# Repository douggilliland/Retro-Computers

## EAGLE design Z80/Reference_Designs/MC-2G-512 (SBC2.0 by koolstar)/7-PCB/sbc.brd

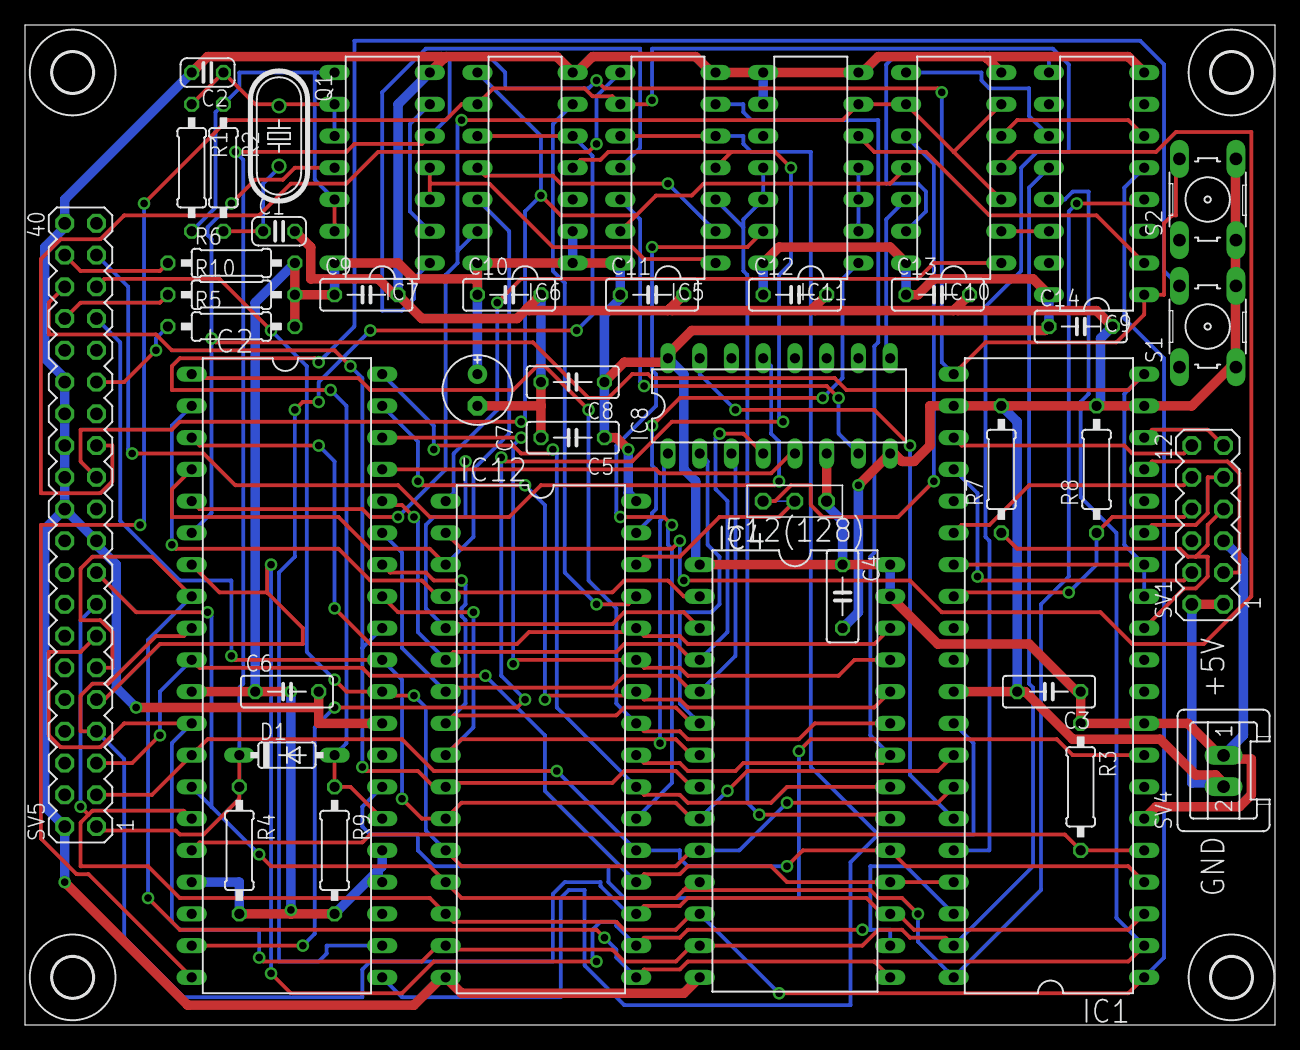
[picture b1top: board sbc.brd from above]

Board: 2 copper layers, 100.0 x 80.0 mm, 47 parts (0 on the bottom side), 74 nets.

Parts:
C1, C2: 22p; C025-024X044
C3, C4, C5, C6, C8, C9, C10, C11, C12, C13, C14: 100n; C050-025X075
C7: .47m; E2,5-6E
D1: 1N4148; DO35-7
H1, H2, H3, H4: 3.2; 3,2
IC1: Z84C4010 SIO/0; DIL40
IC2: Z84C0006; DIL40
IC4: 27C128; DIL28-6
IC5, IC6: 74HCT32; DIL14
IC7: 74HCT00; DIL14
IC8: 74HCT138; DIL16
IC9: 74HCT175; DIL16
IC10, IC11: 74HCT02; DIL14
IC12: AS6C4008 (1008); DIL32
Q1: 7.3728 MHz; HC49U-V
R1: 1M; 0207/10
R2: 1k; 0207/10
R3, R4, R5, R6, R9, R10: 4k7; 0207/10
R7, R8: 10k; 0207/10
S1: WARM; B3F-10XX
S2: COLD; B3F-10XX
SV1: TTY A/B; MA06-2
SV4: IDE Power; S02P
SV5: IDE-CF; MA20-2
U$1: JMP2; JUMP2

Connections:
A0: IC1.34, IC2.30, IC4.10, IC12.12, SV5.35
A1: IC1.33, IC2.31, IC4.9, IC12.11, SV5.33
A2: IC2.32, IC4.8, IC12.10, SV5.36
A3: IC2.33, IC4.7, IC8.1, IC12.9
A4: IC2.34, IC4.6, IC8.2, IC12.8
A5: IC2.35, IC4.5, IC8.3, IC12.7
A6: IC2.36, IC4.4, IC8.4, IC12.6
A7: IC2.37, IC4.3, IC8.5, IC12.5
A8: IC2.38, IC4.25, IC12.27
A9: IC2.39, IC4.24, IC12.26
A10: IC2.40, IC4.21, IC12.23
A11: IC2.1, IC4.23, IC12.25
A12: IC2.2, IC4.2, IC12.4
A13: IC2.3, IC4.26, IC12.28
A14: IC2.4, IC6.12, IC12.3
A15: IC2.5, IC6.13, IC10.3, IC10.6, IC10.9, IC11.6
CLK: IC1.13, IC1.14, IC1.20, IC1.27, IC2.6, IC7.11
CTA: IC1.18, SV1.11
CTB: IC1.23, SV1.12
D0: IC1.40, IC2.14, IC4.11, IC9.4, IC12.13, SV5.17
D1: IC1.1, IC2.15, IC4.12, IC9.5, IC12.14, SV5.15
D2: IC1.39, IC2.12, IC4.13, IC9.12, IC12.15, SV5.13
D3: IC1.2, IC2.8, IC4.15, IC9.13, IC12.17, SV5.11
D4: IC1.38, IC2.7, IC4.16, IC12.18, SV5.9
D5: IC1.3, IC2.9, IC4.17, IC12.19, SV5.7
D6: IC1.37, IC2.10, IC4.18, IC12.20, SV5.5
D7: IC1.4, IC2.13, IC4.19, IC12.21, SV5.3
GND: C1.2, C2.2, C3.2, C4.2, C5.2, C6.2, C7.-, C8.2, C9.2, C10.2, C11.2, C12.2, C13.2, C14.2, IC1.19, IC1.22, IC1.31, IC2.29, IC4.14, IC5.7, IC6.7, IC7.7, IC8.8, IC9.8, IC10.7, IC11.7, IC11.8, IC11.9, IC12.16, R7.2, R8.2, S1.3, S1.4, S2.3, S2.4, SV1.1, SV1.2, SV4.2, SV5.2, SV5.19, SV5.22, SV5.24, SV5.26, SV5.28, SV5.30, SV5.40
INT: IC1.5, IC2.16, R3.2
IORD: IC5.8, SV5.25
IOREQ: IC1.36, IC2.20, IC5.9, IC6.9
IOWR: IC5.13, IC6.8, IC10.11, SV5.23
M1: IC1.8, IC2.27
M15: IC11.1, IC12.31
M16: IC10.4, IC12.2
M17: IC10.10, U$1.1
M18: IC10.1, IC12.1
MEMRD: IC4.22, IC5.6, IC12.24
MEMWR: IC6.6, IC12.29
MREQ: IC2.19, IC5.4, IC6.4
unnamed: IC9.6, IC10.5
unnamed: IC9.2, IC11.5
unnamed: IC7.2, IC7.6
unnamed: IC5.11, IC7.1
unnamed: C2.1, IC7.9, IC7.10, Q1.1, R1.1
unnamed: C1.1, Q1.2, R2.2
unnamed: IC5.2, IC6.11
unnamed: IC5.1, IC7.3, IC7.4
unnamed: IC7.8, IC7.12, IC7.13, R1.2, R2.1
unnamed: IC9.11, IC10.8
unnamed: IC9.14, IC10.2
unnamed: IC11.2, IC11.3, IC11.4
unnamed: IC12.30, U$1.2
unnamed: IC9.9, IC10.13
unnamed: R6.1, SV5.38
unnamed: R10.1, SV5.34
unnamed: R5.1, SV5.29
RAMS: IC11.13, IC12.22
RD: IC1.32, IC2.21, IC5.5, IC5.10
RESET: D1.C, IC1.21, IC7.5, IC9.1, R4.1, S2.2, SV5.1
ROMS: IC4.20, IC5.3, IC11.11, IC11.12
RTA: IC1.17, SV1.3
RTB: IC1.24, SV1.4
RXA: IC1.12, R7.1, SV1.7
RXB: IC1.28, R8.1, SV1.8
TXA: IC1.15, SV1.9
TXB: IC1.26, SV1.10
VCC: C3.1, C4.1, C5.1, C6.1, C7.+, C8.1, C9.1, C10.1, C11.1, C12.1, C13.1, C14.1, IC1.6, IC1.9, IC2.11, IC2.17, IC2.24, IC2.25, IC4.1, IC4.27, IC4.28, IC5.14, IC6.1, IC6.2, IC6.14, IC7.14, IC8.6, IC8.16, IC9.16, IC10.14, IC11.14, IC12.32, R3.1, R4.2, R5.2, R6.2, R9.2, R10.2, SV1.5, SV4.1, U$1.3
WR: IC2.22, IC6.5, IC6.10
WRESET: D1.A, IC2.26, R9.1, S1.2
Y0: IC1.35, IC8.15
Y2: IC8.13, SV5.37
Y6: IC8.9, IC10.12
Y7: IC5.12, IC8.7

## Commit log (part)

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2022-04-15 retro stuff
2022-04-17 Some more FPGA builds
2022-04-18 Builds
2022-04-19 PDP-11 Builds
2022-04-21 docs added
2022-04-23 WORKING TINYBASIC
2022-04-26 FigFORTH works
2022-04-27 FIX LABELS
2022-04-27 Forth in ROM build WIP
2022-04-28 More FIG-Forth docs/builds
2022-04-28 Move files
2022-04-29 Extended RAM test
2022-04-29 External SRAM test works
2022-04-29 More comments
2022-04-29 Fix comments
2022-04-29 PDP-8 and PDP-11 builds
2022-04-30 Make In Box versions of PDP-11
2022-04-30 Built In Box version of PDP-11/45 and PDP-11/70
2022-05-01 More builds
2022-05-01 Another PDP-11 variant plus Forth stuff
2022-05-01 PDP-11/45 in MultiComp box - boots
2022-05-01 Working - Boots RT11V5
2022-05-01 Shuffle PDP-11 docs folders
2022-05-01 Fixed serial port define so SW4 works
2022-05-01 PDP-11/70 in box works
2022-05-02 FLEX DOCS
2022-05-03 6502 stuff
2022-05-09 Working on SD card OS
2022-05-10 Shuffle around OSI OS
2022-05-10 Move helo.c
2022-05-10 Shuffle around folders
2022-05-11 STREAMLINE SD CARD CODE
2022-05-11 ADD CLUSTER OFFSET
2022-05-11 Dump sector number in DIR listing
    Allow user to enter sector number and dump buffer
    Working well
2022-05-13 UK101 C1P docs
2022-05-13 Shuffle OSI files
2022-05-13 More shuffling file
2022-05-30 Shuffle stuff
2022-08-18 DABUG
2022-08-18 Journals
2022-08-18 More OSI
2022-08-19 More OSI stuff
2022-08-26 docs
2022-08-26 TG68 box
2022-09-06 Z80_PSoC code
2022-09-06 Schematic cleanups
2022-09-07 IMPROVEMENTS TO START-UP
2022-09-18 Minor menu tweeks
2022-09-20 65C816 DOCS
2022-09-24 CORSHAM 6800 xSWTBUG
2022-09-25 CORSHAM STUFF
2022-10-06 Bump addressable from 2.7.0 to 2.8.1 in /6502/planck-6502/docs
    Bumps [addressable](https://github.com/sporkmonger/addressable) from 2.7.0 to 2.8.1.
    - [Release notes](https://github.com/sporkmonger/addressable/releases)
    - [Changelog](https://github.com/sporkmonger/addressable/blob/main/CHANGELOG.md)
    - [Commits](https://github.com/sporkmonger/addressable/compare/addressable-2.7.0...addressable-2.8.1)
    ---
    updated-dependencies:
2023-03-15 68K retro
2023-03-30 TinyBasic on 6800 CPU
2024-09-05 Separate 32 and 64 bit assemblers
2024-09-05 loop code
2024-09-05 move folders
2024-09-06 LOOP2
2024-09-07 Code blinks LED
2024-09-07 Rename loop2 as blink
    LED attached to PLD U2-15 with 1.8K resistor to ground. Blinks LED a couple of times a second
2024-09-07 6809 RAM test loop code
2024-09-08 RAM test passes
2024-09-08 updates to ram test
2024-09-08 SRAM Test
2024-09-08 6809 RAM TEST PASSES
2024-09-09 ACIA test code
2024-09-09 AcisTest works
2024-09-11 basic WORKING
2024-09-11 ASSIST-09 DEBUGGER FOR LB-6809
2024-09-11 ASSIST Debugger + ExtBASIC G C000 to run BASIC
2024-09-11 SMITHBUG 4K
2024-09-11 SnithBug plus Forth
2024-09-11 LB-6502 card
2024-09-12 build
2024-09-12 ACIA TEST WORKS
2024-09-13 Move OSI_BASic code to new folder
2024-09-14 Start of a simple monitor
2024-09-15 WORKS
2024-09-15 set scratch
2024-09-16 HEX MEMORY DUMP WORKING
2024-09-16 RAM TEST
2024-09-16 add help messages
2024-09-16 Add LED
2024-09-18 enhanced basic 6502 working on LB-6502-01 card
2024-09-18 SCREEN CAP
2024-09-18 FIX FILE NAME
2024-09-18 Move Enhanced BASIC file
2024-09-18 Enhanced BASIC Bugs and Manual
2024-09-18 Enhanced BASIC patches
    Some of the patches
2024-09-19 Z80 stuff
2024-09-19 move basic to folder
2024-09-19 NASCOM BASIC code
2024-09-19 Z80 builds
2024-10-03 Z80 checkout code
2024-10-04 StringTest code
2024-10-04 Read String works
2024-10-04 NASCOM BASIC works
2024-10-09 More code stuff
2024-10-11 Re-organize Z80 folders
2024-10-11 fix folder
2024-10-14 ADD LED CONTROL
2024-10-16 Z80 CODE
2026-04-08 Bump addressable from 2.7.0 to 2.9.0 in /6502/planck-6502/docs
    Bumps [addressable](https://github.com/sporkmonger/addressable) from 2.7.0 to 2.9.0.
    - [Changelog](https://github.com/sporkmonger/addressable/blob/main/CHANGELOG.md)
    - [Commits](https://github.com/sporkmonger/addressable/compare/addressable-2.7.0...addressable-2.9.0)
    ---
    updated-dependencies:
    - dependency-name: addressable
2026-06-23 Bump concurrent-ruby from 1.1.8 to 1.3.7 in /6502/planck-6502/docs
    Bumps [concurrent-ruby](https://github.com/ruby-concurrency/concurrent-ruby) from 1.1.8 to 1.3.7.
    - [Release notes](https://github.com/ruby-concurrency/concurrent-ruby/releases)
    - [Changelog](https://github.com/ruby-concurrency/concurrent-ruby/blob/master/CHANGELOG.md)
    - [Commits](https://github.com/ruby-concurrency/concurrent-ruby/compare/v1.1.8...v1.3.7)
    ---
    updated-dependencies:
